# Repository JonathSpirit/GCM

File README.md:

# GCM - GCardMother

Copyright (C) 2020 Guillaume Guillet\
Licensed under CERN-OHL-W v2 or later

<table border="0px">
<tr>
<td>
This source describes Open Hardware and is licensed under the CERN-OHL-W v2 or later.
</td>
</tr>
<tr>
<td>
You may redistribute and modify this documentation and make products
using it under the terms of the CERN-OHL-W v2 (https:/cern.ch/cern-ohl).
This documentation is distributed WITHOUT ANY EXPRESS OR IMPLIED
WARRANTY, INCLUDING OF MERCHANTABILITY, SATISFACTORY QUALITY
AND FITNESS FOR A PARTICULAR PURPOSE. Please see the CERN-OHL-W v2
for applicable conditions.
</td>
</tr>
</table>

Made with [Kicad](https://kicad.org/)

## Description
G_CardMother is a homemade without any microcontroller motherboard for 8bits processor compatible with the [MOM1_SPS1 standard](https://github.com/JonathSpirit/GComputer_standard) like [GP8B](https://github.com/JonathSpirit/GP8B)

## Status

Version :
> GCM_V5.0

Status :
> Testing ...

Known issues :
> 4 light impact bugs, 1 high impact bug, (Please to avoid any problems wait the V5.1 release)

## Block diagram

[Block diagram (.pdf)](documents/blockDiagram/GCM_blockDiagram.pdf)

## Main features

- Follow the [MOM1_SPS1](https://github.com/JonathSpirit/GComputer_standard) standard.

- A controllable frequency of 50Mhz divisible by multiples of two up to a division of 65536.

- The same separate controllable frequency divisible by multiples of two for peripherals.

- 4 peripherals slot (that follow standard [PP1](https://github.com/JonathSpirit/GComputer_standard)).

- 2 [MM1](https://github.com/JonathSpirit/GComputer_standard) memory slot with address extension.

- Readable code source switching from the 2 memory slot.

- Redirection of the writing buses.

- Accessible debug pins.

## Motherboard standard
This motherboard, follow the [MOM1_SPS1](https://github.com/JonathSpirit/GComputer_standard) standard

## Compatibility
Compatible with all processor following the [SPS1](https://github.com/JonathSpirit/GComputer_standard) standard

| Processor     | Compatibility |
| ------------- | ------------- |
| [GP8B_V4.x](https://github.com/JonathSpirit/GP8B/tree/V4.0)  |   |
| [GP8B_V5.x](https://github.com/JonathSpirit/GP8B/tree/V5.0)  |   |

 `Fully compatible`\
 `Semi compatible`\
 `No compatible`

## Documents
[Block diagram (.pdf)](documents/blockDiagram/GCM_blockDiagram.pdf)

[Schematics (.pdf)](documents/GCM_schematics.pdf)

[Materials (.pdf)](documents/GCM_materials.pdf)

[Datasheet (.pdf)](documents/GCM_datasheet.pdf)

## Contributing / Questions
Please see [Contributing file](CONTRIBUTING.md)

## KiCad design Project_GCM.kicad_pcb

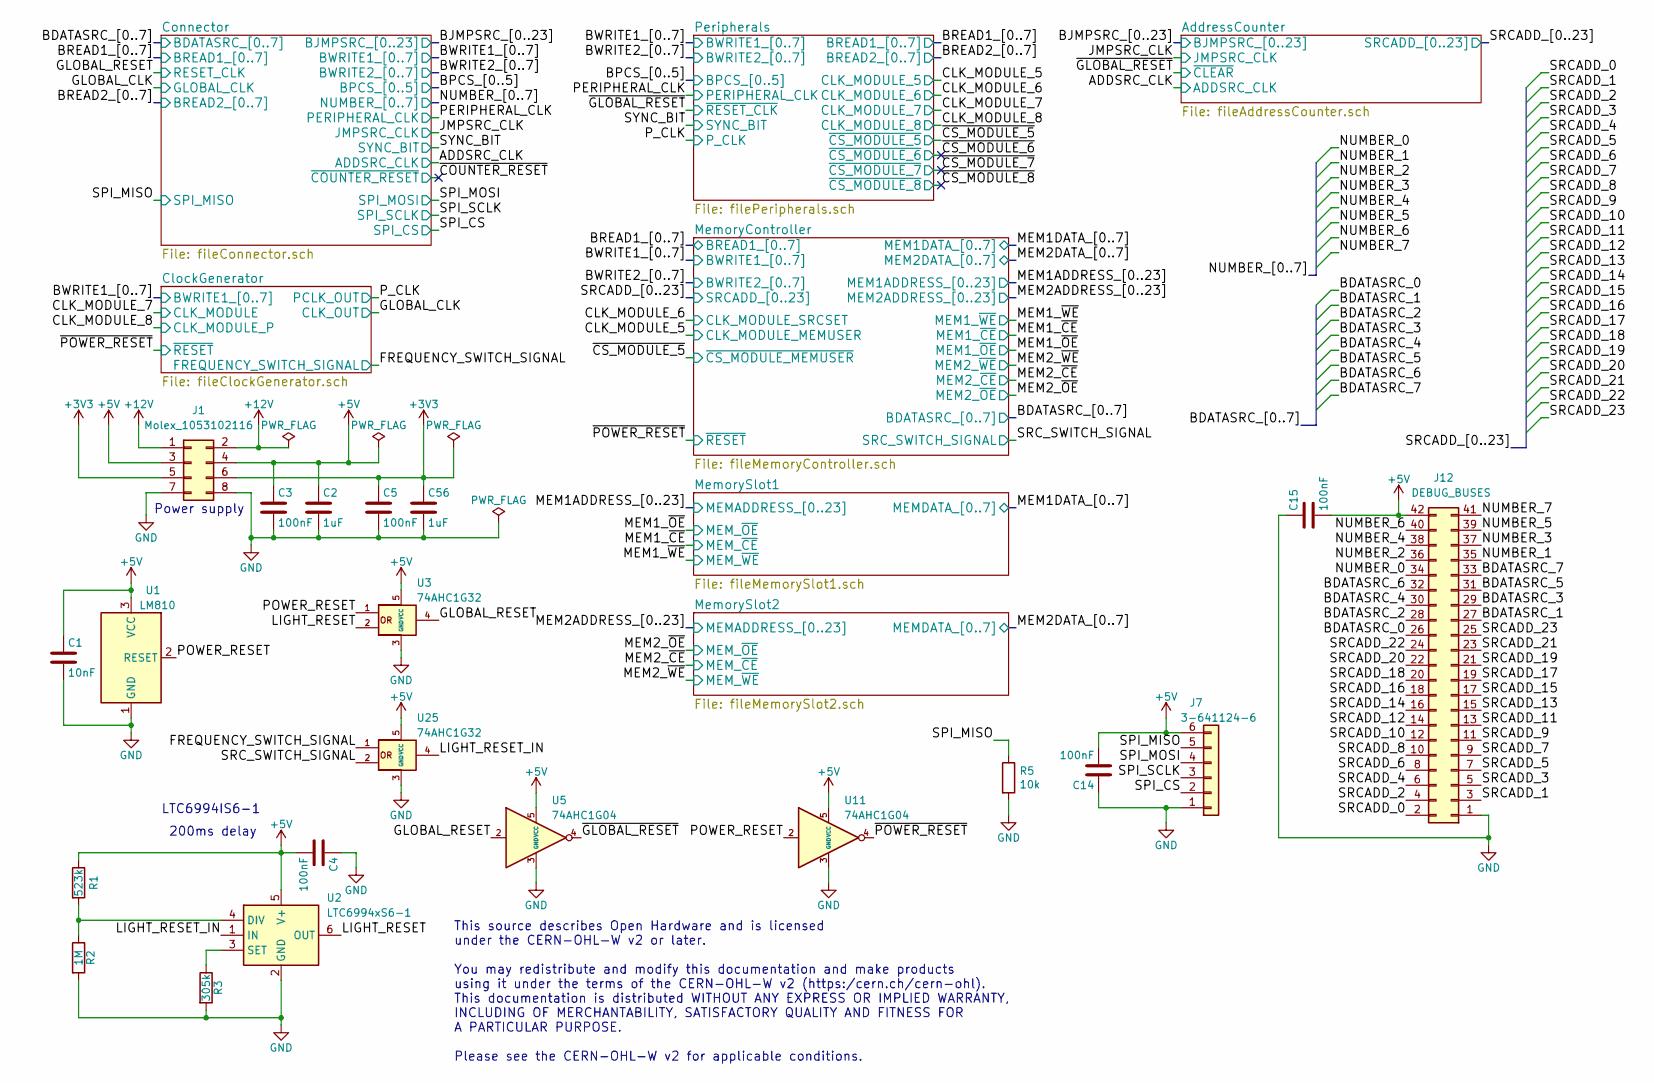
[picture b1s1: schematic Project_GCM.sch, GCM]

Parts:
C1: 10nF; C_0805_2012Metric
C2, C56: 1uF; C_0805_2012Metric
C3, C4, C5, C14, C15: 100nF; C_0805_2012Metric
J1: Molex_1053102116; Molex_Nano-Fit_105310-xx08_2x04_P2.50mm_Vertical
J7: 3-641124-6; TE_3-641124-6
J12: DEBUG_BUSES; PinHeader_2x21_P2.54mm_Vertical
R1: 523k; R_0805_2012Metric
R2: 1M; R_0805_2012Metric
R3: 305k; R_0805_2012Metric
R5: 10k; R_0805_2012Metric
U1: LM810; SOT-23
U2: LTC6994xS6-1; TSOT-23-6
U3, U25: 74AHC1G32; SOT-23-5
U5, U11: 74AHC1G04; SOT-23-5

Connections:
+5V: C1.1, C2.1, C3.1, C4.2, C14.2, C15.2, J1.3, J1.4, J7.6, J12.42, R1.1, U1.3 (VCC), U2.5 (V+), U3.5 (VCC), U5.5 (VCC), U11.5 (VCC), U25.5 (VCC); also elsewhere on the board
+12V: J1.1, J1.2
/BDATASRC_0: J12.26; also elsewhere on the board
/BDATASRC_1: J12.27; also elsewhere on the board
/BDATASRC_2: J12.28; also elsewhere on the board
/BDATASRC_3: J12.29; also elsewhere on the board
/BDATASRC_4: J12.30; also elsewhere on the board
/BDATASRC_5: J12.31; also elsewhere on the board
/BDATASRC_6: J12.32; also elsewhere on the board
/BDATASRC_7: J12.33; also elsewhere on the board
/CLK_MODULE_6: U25.2; also elsewhere on the board
/FREQUENCY_SWITCH_SIGNAL: U25.1; also elsewhere on the board
/GLOBAL_RESET: U3.4, U5.2; also elsewhere on the board
/LIGHT_RESET: U2.6 (OUT), U3.2
/LIGHT_RESET_IN: U2.1 (IN), U25.4
/NUMBER_0: J12.34; also elsewhere on the board
/NUMBER_1: J12.35; also elsewhere on the board
/NUMBER_2: J12.36; also elsewhere on the board
/NUMBER_3: J12.37; also elsewhere on the board
/NUMBER_4: J12.38; also elsewhere on the board
/NUMBER_5: J12.39; also elsewhere on the board
/NUMBER_6: J12.40; also elsewhere on the board
/NUMBER_7: J12.41; also elsewhere on the board
/POWER_RESET: U1.2 (RESET), U3.1, U11.2
/SPI_CS: J7.2; also elsewhere on the board
/SPI_MISO: J7.5, R5.1; also elsewhere on the board
/SPI_MOSI: J7.4; also elsewhere on the board
/SPI_SCLK: J7.3; also elsewhere on the board
/SRCADD_0: J12.2; also elsewhere on the board
/SRCADD_1: J12.3; also elsewhere on the board
/SRCADD_2: J12.4; also elsewhere on the board
/SRCADD_3: J12.5; also elsewhere on the board
/SRCADD_4: J12.6; also elsewhere on the board
/SRCADD_5: J12.7; also elsewhere on the board
/SRCADD_6: J12.8; also elsewhere on the board
/SRCADD_7: J12.9; also elsewhere on the board
/SRCADD_8: J12.10; also elsewhere on the board
/SRCADD_9: J12.11; also elsewhere on the board
/SRCADD_10: J12.12; also elsewhere on the board
/SRCADD_11: J12.13; also elsewhere on the board
/SRCADD_12: J12.14; also elsewhere on the board
/SRCADD_13: J12.15; also elsewhere on the board
/SRCADD_14: J12.16; also elsewhere on the board
/SRCADD_15: J12.17; also elsewhere on the board
/SRCADD_16: J12.18; also elsewhere on the board
/SRCADD_17: J12.19; also elsewhere on the board
/SRCADD_18: J12.20; also elsewhere on the board
/SRCADD_19: J12.21; also elsewhere on the board
/SRCADD_20: J12.22; also elsewhere on the board
/SRCADD_21: J12.23; also elsewhere on the board
/SRCADD_22: J12.24; also elsewhere on the board
/SRCADD_23: J12.25; also elsewhere on the board
/~GLOBAL_RESET: U5.4; also elsewhere on the board
/~POWER_RESET: U11.4; also elsewhere on the board
GND: C1.2, C2.2, C3.2, C4.1, C5.2, C14.1, C15.1, C56.2, J1.7, J1.8, J7.1, J12.1, R2.2, R3.2, R5.2, U1.1 (GND), U2.2 (GND), U3.3 (GND), U5.3 (GND), U11.3 (GND), U25.3 (GND); also elsewhere on the board
unnamed: R1.2, R2.1, U2.4 (DIV)
unnamed: R3.1, U2.3 (SET)

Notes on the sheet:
200ms delay
LTC6994IS6-1
This source describes Open Hardware and is licensed under the CERN-OHL-W v2 or later. You may redistribute and modify this documentation and make products using it under the terms of the CERN-OHL-W v2 (https:/cern.ch/cern-ohl). This documentation is distributed WITHOUT ANY EXPRESS OR IMPLIED WARRAN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
Power supply

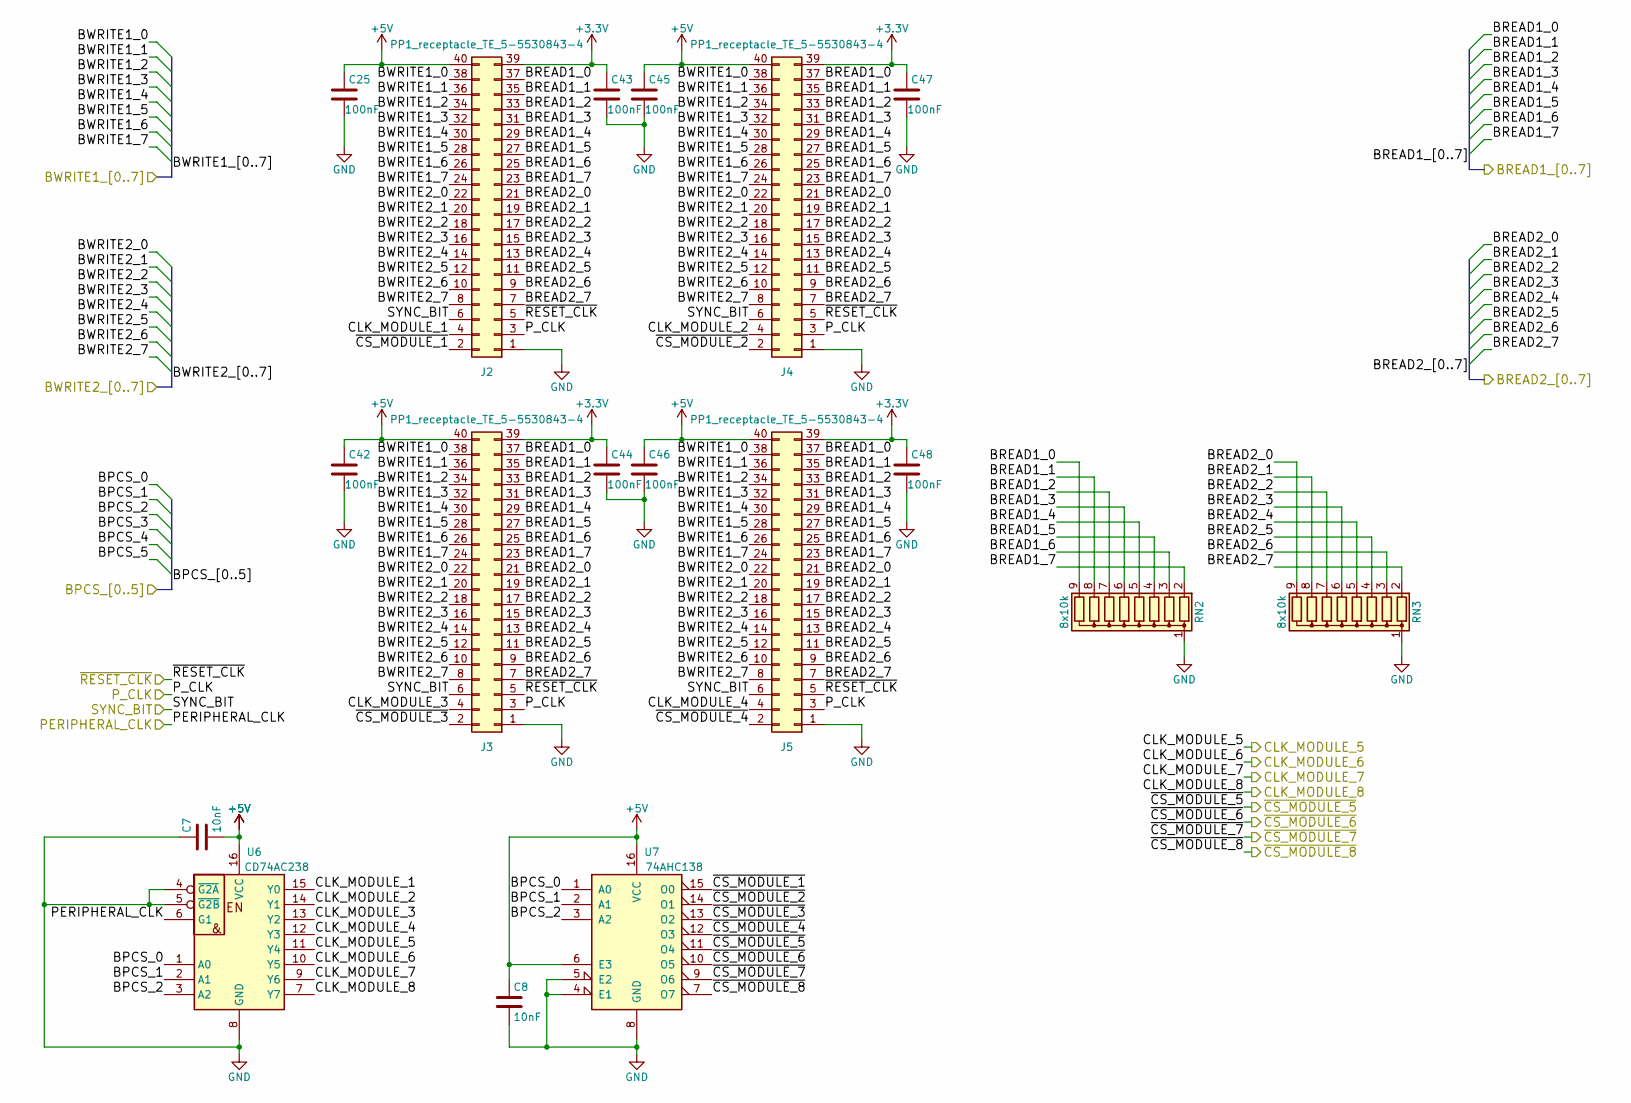
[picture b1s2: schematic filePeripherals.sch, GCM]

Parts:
C7, C8: 10nF; C_0805_2012Metric
C25, C42, C43, C44, C45, C46, C47, C48: 100nF; C_0805_2012Metric
J2, J3, J4, J5: PP1_receptacle_TE_5-5530843-4; TE_5-5530843-4
RN2, RN3: 8x10k; R_Array_SIP9
U6: CD74AC238; SOP-16_3.9x9.9mm_P1.27mm
U7: 74AHC138; SOIC-16W_5.3x10.2mm_P1.27mm

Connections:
+5V: C7.2, C8.1, C25.1, C42.1, C45.1, C46.1, J2.40, J3.40, J4.40, J5.40, U6.16 (VCC), U7.6 (E3), U7.16 (VCC); also elsewhere on the board
/CLK_MODULE_5: U6.11 (Y4); also elsewhere on the board
/CLK_MODULE_6: U6.10 (Y5); also elsewhere on the board
/CLK_MODULE_7: U6.9 (Y6); also elsewhere on the board
/CLK_MODULE_8: U6.7 (Y7); also elsewhere on the board
/ClockGenerator/BWRITE1_0: J2.38, J3.38, J4.38, J5.38; also elsewhere on the board
/ClockGenerator/BWRITE1_1: J2.36, J3.36, J4.36, J5.36; also elsewhere on the board
/ClockGenerator/BWRITE1_2: J2.34, J3.34, J4.34, J5.34; also elsewhere on the board
/ClockGenerator/BWRITE1_3: J2.32, J3.32, J4.32, J5.32; also elsewhere on the board
/ClockGenerator/BWRITE1_4: J2.30, J3.30, J4.30, J5.30; also elsewhere on the board
/ClockGenerator/BWRITE1_5: J2.28, J3.28, J4.28, J5.28; also elsewhere on the board
/ClockGenerator/BWRITE1_6: J2.26, J3.26, J4.26, J5.26; also elsewhere on the board
/ClockGenerator/BWRITE1_7: J2.24, J3.24, J4.24, J5.24; also elsewhere on the board
/Connector/BPCS_0: U6.1 (A0), U7.1 (A0); also elsewhere on the board
/Connector/BPCS_1: U6.2 (A1), U7.2 (A1); also elsewhere on the board
/Connector/BPCS_2: U6.3 (A2), U7.3 (A2); also elsewhere on the board
/Connector/BREAD1_0: J2.37, J3.37, J4.37, J5.37, RN2.9 (R8); also elsewhere on the board
/Connector/BREAD1_1: J2.35, J3.35, J4.35, J5.35, RN2.8 (R7); also elsewhere on the board
/Connector/BREAD1_2: J2.33, J3.33, J4.33, J5.33, RN2.7 (R6); also elsewhere on the board
/Connector/BREAD1_3: J2.31, J3.31, J4.31, J5.31, RN2.6 (R5); also elsewhere on the board
/Connector/BREAD1_4: J2.29, J3.29, J4.29, J5.29, RN2.5 (R4); also elsewhere on the board
/Connector/BREAD1_5: J2.27, J3.27, J4.27, J5.27, RN2.4 (R3); also elsewhere on the board
/Connector/BREAD1_6: J2.25, J3.25, J4.25, J5.25, RN2.3 (R2); also elsewhere on the board
/Connector/BREAD1_7: J2.23, J3.23, J4.23, J5.23, RN2.2 (R1); also elsewhere on the board
/Connector/BREAD2_0: J2.21, J3.21, J4.21, J5.21, RN3.9 (R8); also elsewhere on the board
/Connector/BREAD2_1: J2.19, J3.19, J4.19, J5.19, RN3.8 (R7); also elsewhere on the board
/Connector/BREAD2_2: J2.17, J3.17, J4.17, J5.17, RN3.7 (R6); also elsewhere on the board
/Connector/BREAD2_3: J2.15, J3.15, J4.15, J5.15, RN3.6 (R5); also elsewhere on the board
/Connector/BREAD2_4: J2.13, J3.13, J4.13, J5.13, RN3.5 (R4); also elsewhere on the board
/Connector/BREAD2_5: J2.11, J3.11, J4.11, J5.11, RN3.4 (R3); also elsewhere on the board
/Connector/BREAD2_6: J2.9, J3.9, J4.9, J5.9, RN3.3 (R2); also elsewhere on the board
/Connector/BREAD2_7: J2.7, J3.7, J4.7, J5.7, RN3.2 (R1); also elsewhere on the board
/Connector/BWRITE2_0: J2.22, J3.22, J4.22, J5.22; also elsewhere on the board
/Connector/BWRITE2_1: J2.20, J3.20, J4.20, J5.20; also elsewhere on the board
/Connector/BWRITE2_2: J2.18, J3.18, J4.18, J5.18; also elsewhere on the board
/Connector/BWRITE2_3: J2.16, J3.16, J4.16, J5.16; also elsewhere on the board
/Connector/BWRITE2_4: J2.14, J3.14, J4.14, J5.14; also elsewhere on the board
/Connector/BWRITE2_5: J2.12, J3.12, J4.12, J5.12; also elsewhere on the board
/Connector/BWRITE2_6: J2.10, J3.10, J4.10, J5.10; also elsewhere on the board
/Connector/BWRITE2_7: J2.8, J3.8, J4.8, J5.8; also elsewhere on the board
/PERIPHERAL_CLK: U6.6 (G1); also elsewhere on the board
/P_CLK: J2.3, J3.3, J4.3, J5.3; also elsewhere on the board
/Peripherals/CLK_MODULE_1: J2.4, U6.15 (Y0)
/Peripherals/CLK_MODULE_2: J4.4, U6.14 (Y1)
/Peripherals/CLK_MODULE_3: J3.4, U6.13 (Y2)
/Peripherals/CLK_MODULE_4: J5.4, U6.12 (Y3)
/Peripherals/~CS_MODULE_1: J2.2, U7.15 (O0)
/Peripherals/~CS_MODULE_2: J4.2, U7.14 (O1)
/Peripherals/~CS_MODULE_3: J3.2, U7.13 (O2)
/Peripherals/~CS_MODULE_4: J5.2, U7.12 (O3)
/SYNC_BIT: J2.6, J3.6, J4.6, J5.6; also elsewhere on the board
/~CS_MODULE_5: U7.11 (O4); also elsewhere on the board
/~CS_MODULE_6: U7.10 (O5)
/~CS_MODULE_7: U7.9 (O6)
/~CS_MODULE_8: U7.7 (O7)
/~GLOBAL_RESET: J2.5, J3.5, J4.5, J5.5; also elsewhere on the board
GND: C7.1, C8.2, C25.2, C42.2, C43.2, C44.2, C45.2, C46.2, C47.2, C48.2, J2.1, J3.1, J4.1, J5.1, RN2.1 (common), RN3.1 (common), U6.4 (~G2A), U6.5 (~G2B), U6.8 (GND), U7.4 (E1), U7.5 (E2), U7.8 (GND); also elsewhere on the board

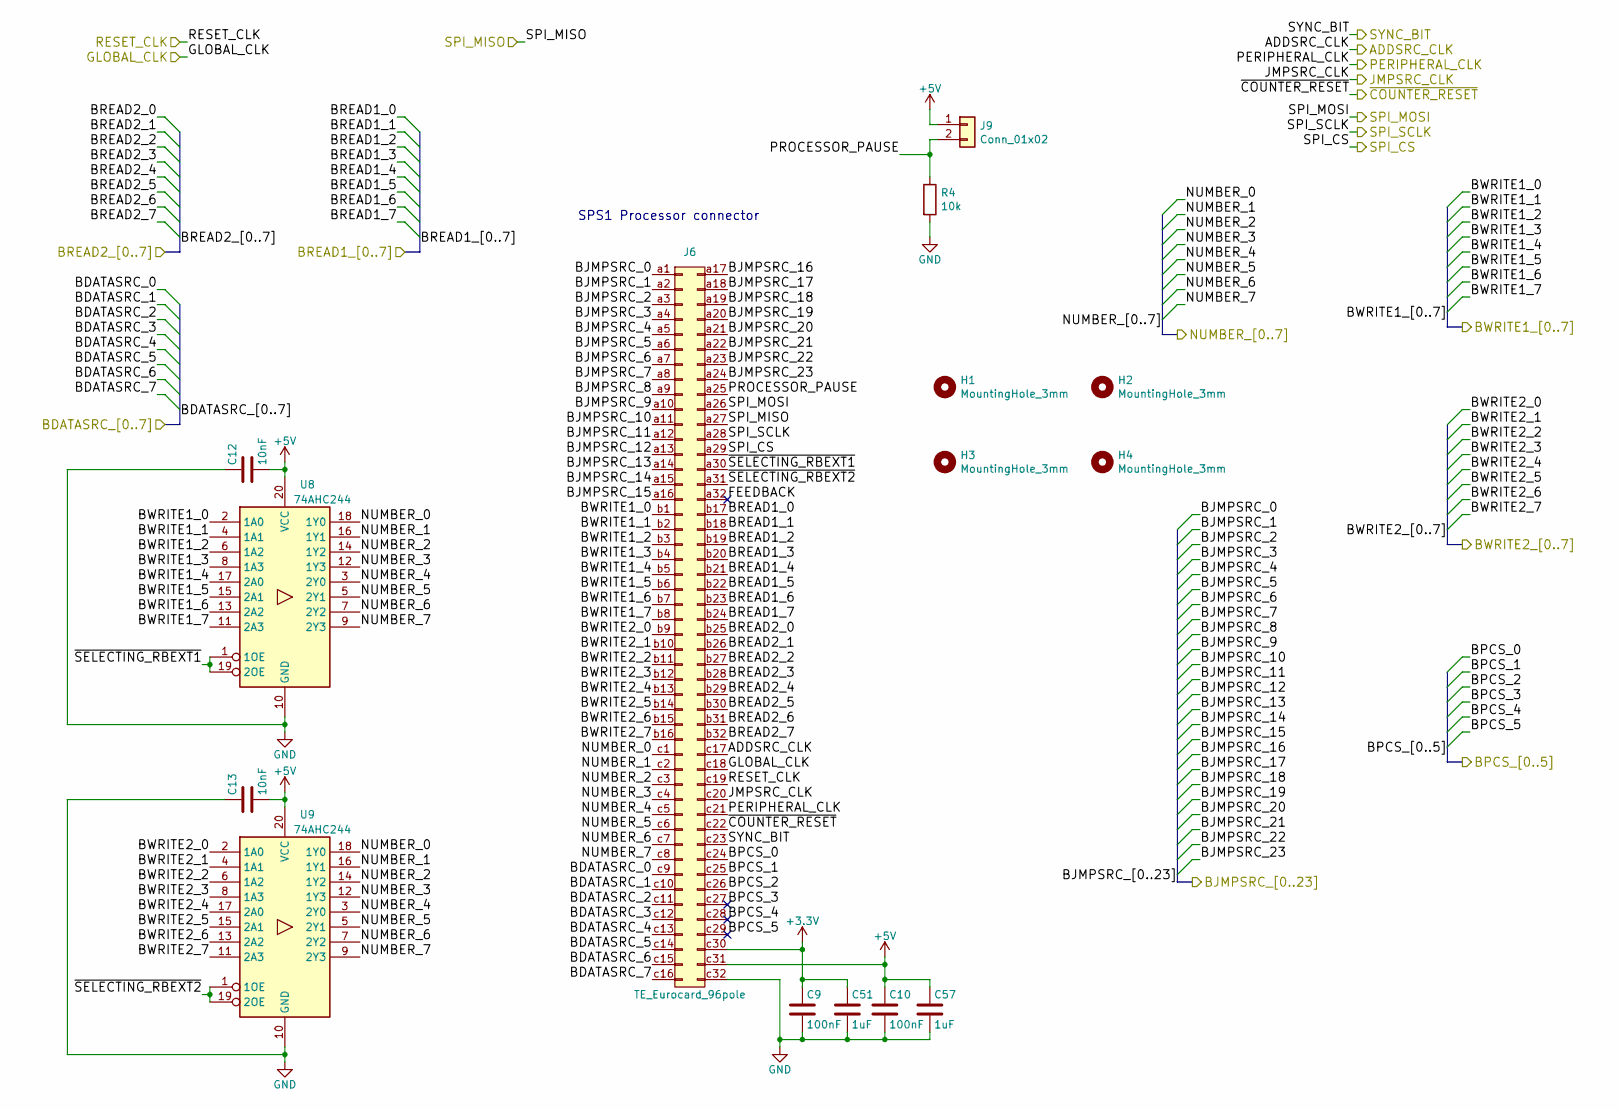
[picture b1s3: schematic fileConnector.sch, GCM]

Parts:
C9, C10: 100nF; C_0805_2012Metric
C12, C13: 10nF; C_0805_2012Metric
C51, C57: 1uF; C_0805_2012Metric
H1, H2, H3, H4: MountingHole_3mm
J6: TE_Eurocard_96pole; Eurocard_5536475-1_Inv
J9: Conn_01x02; PinHeader_1x02_P2.54mm_Vertical
R4: 10k; R_0805_2012Metric
U8, U9: 74AHC244; SOIC-20W_7.5x12.8mm_P1.27mm

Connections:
+5V: C10.1, C12.2, C13.2, C57.1, J6.c31, J9.1, U8.20 (VCC), U9.20 (VCC); also elsewhere on the board
/ADDSRC_CLK: J6.c17; also elsewhere on the board
/AddressCounter/BJMPSRC_0: J6.a1; also elsewhere on the board
/AddressCounter/BJMPSRC_1: J6.a2; also elsewhere on the board
/AddressCounter/BJMPSRC_2: J6.a3; also elsewhere on the board
/AddressCounter/BJMPSRC_3: J6.a4; also elsewhere on the board
/AddressCounter/BJMPSRC_4: J6.a5; also elsewhere on the board
/AddressCounter/BJMPSRC_5: J6.a6; also elsewhere on the board
/AddressCounter/BJMPSRC_6: J6.a7; also elsewhere on the board
/AddressCounter/BJMPSRC_7: J6.a8; also elsewhere on the board
/AddressCounter/BJMPSRC_8: J6.a9; also elsewhere on the board
/AddressCounter/BJMPSRC_9: J6.a10; also elsewhere on the board
/AddressCounter/BJMPSRC_10: J6.a11; also elsewhere on the board
/AddressCounter/BJMPSRC_11: J6.a12; also elsewhere on the board
/AddressCounter/BJMPSRC_12: J6.a13; also elsewhere on the board
/AddressCounter/BJMPSRC_13: J6.a14; also elsewhere on the board
/AddressCounter/BJMPSRC_14: J6.a15; also elsewhere on the board
/AddressCounter/BJMPSRC_15: J6.a16; also elsewhere on the board
/AddressCounter/BJMPSRC_16: J6.a17; also elsewhere on the board
/AddressCounter/BJMPSRC_17: J6.a18; also elsewhere on the board
/AddressCounter/BJMPSRC_18: J6.a19; also elsewhere on the board
/AddressCounter/BJMPSRC_19: J6.a20; also elsewhere on the board
/AddressCounter/BJMPSRC_20: J6.a21; also elsewhere on the board
/AddressCounter/BJMPSRC_21: J6.a22; also elsewhere on the board
/AddressCounter/BJMPSRC_22: J6.a23; also elsewhere on the board
/AddressCounter/BJMPSRC_23: J6.a24; also elsewhere on the board
/BDATASRC_0: J6.c9; also elsewhere on the board
/BDATASRC_1: J6.c10; also elsewhere on the board
/BDATASRC_2: J6.c11; also elsewhere on the board
/BDATASRC_3: J6.c12; also elsewhere on the board
/BDATASRC_4: J6.c13; also elsewhere on the board
/BDATASRC_5: J6.c14; also elsewhere on the board
/BDATASRC_6: J6.c15; also elsewhere on the board
/BDATASRC_7: J6.c16; also elsewhere on the board
/ClockGenerator/BWRITE1_0: J6.b1, U8.2 (1A0); also elsewhere on the board
/ClockGenerator/BWRITE1_1: J6.b2, U8.4 (1A1); also elsewhere on the board
/ClockGenerator/BWRITE1_2: J6.b3, U8.6 (1A2); also elsewhere on the board
/ClockGenerator/BWRITE1_3: J6.b4, U8.8 (1A3); also elsewhere on the board
/ClockGenerator/BWRITE1_4: J6.b5, U8.17 (2A0); also elsewhere on the board
/ClockGenerator/BWRITE1_5: J6.b6, U8.15 (2A1); also elsewhere on the board
/ClockGenerator/BWRITE1_6: J6.b7, U8.13 (2A2); also elsewhere on the board
/ClockGenerator/BWRITE1_7: J6.b8, U8.11 (2A3); also elsewhere on the board
/Connector/BPCS_0: J6.c24; also elsewhere on the board
/Connector/BPCS_1: J6.c25; also elsewhere on the board
/Connector/BPCS_2: J6.c26; also elsewhere on the board
/Connector/BPCS_3: J6.c27
/Connector/BPCS_4: J6.c28
/Connector/BPCS_5: J6.c29
/Connector/BREAD1_0: J6.b17; also elsewhere on the board
/Connector/BREAD1_1: J6.b18; also elsewhere on the board
/Connector/BREAD1_2: J6.b19; also elsewhere on the board
/Connector/BREAD1_3: J6.b20; also elsewhere on the board
/Connector/BREAD1_4: J6.b21; also elsewhere on the board
/Connector/BREAD1_5: J6.b22; also elsewhere on the board
/Connector/BREAD1_6: J6.b23; also elsewhere on the board
/Connector/BREAD1_7: J6.b24; also elsewhere on the board
/Connector/BREAD2_0: J6.b25; also elsewhere on the board
/Connector/BREAD2_1: J6.b26; also elsewhere on the board
/Connector/BREAD2_2: J6.b27; also elsewhere on the board
/Connector/BREAD2_3: J6.b28; also elsewhere on the board
/Connector/BREAD2_4: J6.b29; also elsewhere on the board
/Connector/BREAD2_5: J6.b30; also elsewhere on the board
/Connector/BREAD2_6: J6.b31; also elsewhere on the board
/Connector/BREAD2_7: J6.b32; also elsewhere on the board
/Connector/BWRITE2_0: J6.b9, U9.2 (1A0); also elsewhere on the board
/Connector/BWRITE2_1: J6.b10, U9.4 (1A1); also elsewhere on the board
/Connector/BWRITE2_2: J6.b11, U9.6 (1A2); also elsewhere on the board
/Connector/BWRITE2_3: J6.b12, U9.8 (1A3); also elsewhere on the board
/Connector/BWRITE2_4: J6.b13, U9.17 (2A0); also elsewhere on the board
/Connector/BWRITE2_5: J6.b14, U9.15 (2A1); also elsewhere on the board
/Connector/BWRITE2_6: J6.b15, U9.13 (2A2); also elsewhere on the board
/Connector/BWRITE2_7: J6.b16, U9.11 (2A3); also elsewhere on the board
/Connector/FEEDBACK: J6.a32
/Connector/PROCESSOR_PAUSE: J6.a25, J9.2, R4.1
/Connector/~SELECTING_RBEXT1: J6.a30, U8.1 (1OE), U8.19 (2OE)
/Connector/~SELECTING_RBEXT2: J6.a31, U9.1 (1OE), U9.19 (2OE)
/GLOBAL_CLK: J6.c18; also elsewhere on the board
/GLOBAL_RESET: J6.c19; also elsewhere on the board
/JMPSRC_CLK: J6.c20; also elsewhere on the board
/NUMBER_0: J6.c1, U8.18 (1Y0), U9.18 (1Y0); also elsewhere on the board
/NUMBER_1: J6.c2, U8.16 (1Y1), U9.16 (1Y1); also elsewhere on the board
/NUMBER_2: J6.c3, U8.14 (1Y2), U9.14 (1Y2); also elsewhere on the board
/NUMBER_3: J6.c4, U8.12 (1Y3), U9.12 (1Y3); also elsewhere on the board
/NUMBER_4: J6.c5, U8.3 (2Y0), U9.3 (2Y0); also elsewhere on the board
/NUMBER_5: J6.c6, U8.5 (2Y1), U9.5 (2Y1); also elsewhere on the board
/NUMBER_6: J6.c7, U8.7 (2Y2), U9.7 (2Y2); also elsewhere on the board
/NUMBER_7: J6.c8, U8.9 (2Y3), U9.9 (2Y3); also elsewhere on the board
/PERIPHERAL_CLK: J6.c21; also elsewhere on the board
/SPI_CS: J6.a29; also elsewhere on the board
/SPI_MISO: J6.a27; also elsewhere on the board
/SPI_MOSI: J6.a26; also elsewhere on the board
/SPI_SCLK: J6.a28; also elsewhere on the board
/SYNC_BIT: J6.c23; also elsewhere on the board
/~COUNTER_RESET: J6.c22
GND: C9.2, C10.2, C12.1, C13.1, C51.2, C57.2, J6.c32, R4.2, U8.10 (GND), U9.10 (GND); also elsewhere on the board

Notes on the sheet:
SPS1 Processor connector

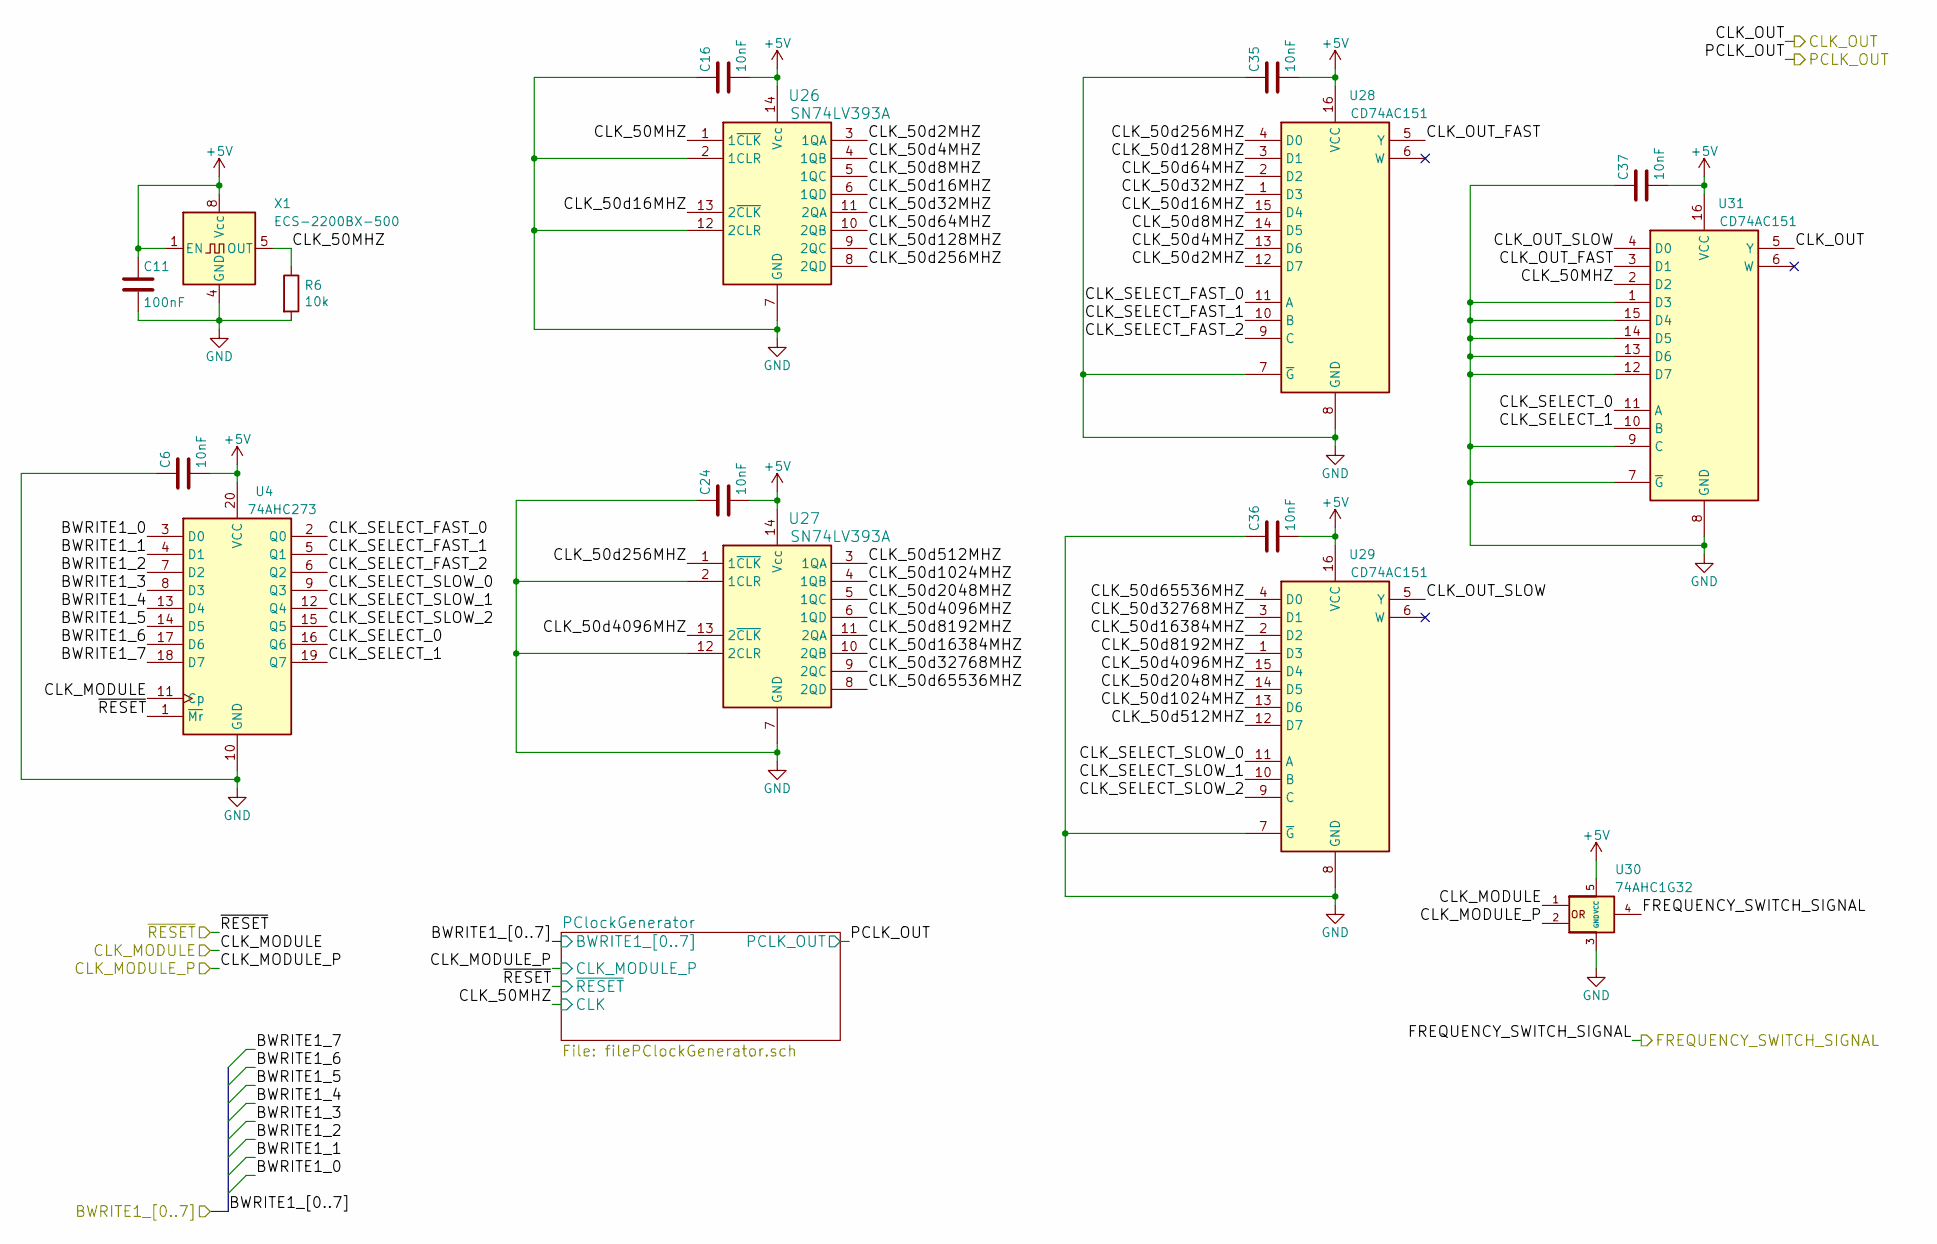
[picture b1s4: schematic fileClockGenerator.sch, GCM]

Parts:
C6, C16, C24, C35, C36, C37: 10nF; C_0805_2012Metric
C11: 100nF; C_0805_2012Metric
R6: 10k; R_0805_2012Metric
U4: 74AHC273; SOIC-20W_7.5x12.8mm_P1.27mm
U26, U27: SN74LV393A; SOIC-14_3.9x8.7mm_P1.27mm
U28, U29, U31: CD74AC151; SOP-16_3.9x9.9mm_P1.27mm
U30: 74AHC1G32; SOT-23-5
X1: ECS-2200BX-500; Oscillator_DIP-8

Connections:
+5V: C6.2, C11.1, C16.2, C24.2, C35.2, C36.2, C37.2, U4.20 (VCC), U26.14 (Vcc), U27.14 (Vcc), U28.16 (VCC), U29.16 (VCC), U30.5 (VCC), U31.16 (VCC), X1.1 (EN), X1.8 (Vcc); also elsewhere on the board
/CLK_MODULE_7: U4.11 (Cp), U30.1; also elsewhere on the board
/CLK_MODULE_8: U30.2; also elsewhere on the board
/ClockGenerator/BWRITE1_0: U4.3 (D0); also elsewhere on the board
/ClockGenerator/BWRITE1_1: U4.4 (D1); also elsewhere on the board
/ClockGenerator/BWRITE1_2: U4.7 (D2); also elsewhere on the board
/ClockGenerator/BWRITE1_3: U4.8 (D3); also elsewhere on the board
/ClockGenerator/BWRITE1_4: U4.13 (D4); also elsewhere on the board
/ClockGenerator/BWRITE1_5: U4.14 (D5); also elsewhere on the board
/ClockGenerator/BWRITE1_6: U4.17 (D6); also elsewhere on the board
/ClockGenerator/BWRITE1_7: U4.18 (D7); also elsewhere on the board
/ClockGenerator/CLK_50MHZ: R6.1, U26.1 (1~CLK), U31.2 (D2), X1.5 (OUT); also elsewhere on the board
/ClockGenerator/CLK_50d2MHZ: U26.3 (1QA), U28.12 (D7)
/ClockGenerator/CLK_50d4MHZ: U26.4 (1QB), U28.13 (D6)
/ClockGenerator/CLK_50d8MHZ: U26.5 (1QC), U28.14 (D5)
/ClockGenerator/CLK_50d16MHZ: U26.6 (1QD), U26.13 (2~CLK), U28.15 (D4)
/ClockGenerator/CLK_50d32MHZ: U26.11 (2QA), U28.1 (D3)
/ClockGenerator/CLK_50d64MHZ: U26.10 (2QB), U28.2 (D2)
/ClockGenerator/CLK_50d128MHZ: U26.9 (2QC), U28.3 (D1)
/ClockGenerator/CLK_50d256MHZ: U26.8 (2QD), U27.1 (1~CLK), U28.4 (D0)
/ClockGenerator/CLK_50d512MHZ: U27.3 (1QA), U29.12 (D7)
/ClockGenerator/CLK_50d1024MHZ: U27.4 (1QB), U29.13 (D6)
/ClockGenerator/CLK_50d2048MHZ: U27.5 (1QC), U29.14 (D5)
/ClockGenerator/CLK_50d4096MHZ: U27.6 (1QD), U27.13 (2~CLK), U29.15 (D4)
/ClockGenerator/CLK_50d8192MHZ: U27.11 (2QA), U29.1 (D3)
/ClockGenerator/CLK_50d16384MHZ: U27.10 (2QB), U29.2 (D2)
/ClockGenerator/CLK_50d32768MHZ: U27.9 (2QC), U29.3 (D1)
/ClockGenerator/CLK_50d65536MHZ: U27.8 (2QD), U29.4 (D0)
/ClockGenerator/CLK_OUT_FAST: U28.5 (Y), U31.3 (D1)
/ClockGenerator/CLK_OUT_SLOW: U29.5 (Y), U31.4 (D0)
/ClockGenerator/CLK_SELECT_0: U4.16 (Q6), U31.11 (A)
/ClockGenerator/CLK_SELECT_1: U4.19 (Q7), U31.10 (B)
/ClockGenerator/CLK_SELECT_FAST_0: U4.2 (Q0), U28.11 (A)
/ClockGenerator/CLK_SELECT_FAST_1: U4.5 (Q1), U28.10 (B)
/ClockGenerator/CLK_SELECT_FAST_2: U4.6 (Q2), U28.9 (C)
/ClockGenerator/CLK_SELECT_SLOW_0: U4.9 (Q3), U29.11 (A)
/ClockGenerator/CLK_SELECT_SLOW_1: U4.12 (Q4), U29.10 (B)
/ClockGenerator/CLK_SELECT_SLOW_2: U4.15 (Q5), U29.9 (C)
/FREQUENCY_SWITCH_SIGNAL: U30.4; also elsewhere on the board
/GLOBAL_CLK: U31.5 (Y); also elsewhere on the board
/~POWER_RESET: U4.1 (~Mr); also elsewhere on the board
GND: C6.1, C11.2, C16.1, C24.1, C35.1, C36.1, C37.1, R6.2, U4.10 (GND), U26.2 (1CLR), U26.7 (GND), U26.12 (2CLR), U27.2 (1CLR), U27.7 (GND), U27.12 (2CLR), U28.7 (~G), U28.8 (GND), U29.7 (~G), U29.8 (GND), U30.3 (GND), U31.1 (D3), U31.7 (~G), U31.8 (GND), U31.9 (C), U31.12 (D7), U31.13 (D6), U31.14 (D5), U31.15 (D4), X1.4 (GND); also elsewhere on the board

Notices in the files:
Project_GCM.kicad_pcb:
Copyright Guillaume Guillet 2021
